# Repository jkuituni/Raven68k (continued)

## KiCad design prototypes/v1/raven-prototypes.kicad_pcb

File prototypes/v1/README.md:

# Raven68k Prototype Build

## Revision 0
This is the first publicly available release of the Raven68k project as generated and sent to [JLCPCB (Shenzhen JLC Electronics Co., Ltd.)](https://jlcpcb.com) for manufacture on November 5th, 2018.  As this is the very first prototype board, one should expect things that don't make sense or are outright wrong.  You have been warned. ;)

## Software 

The Rev0 software is available in this repository under the /rom/v1 directory.

## RAM and ROM locations

| Type 	| Start Address 	| Size   	|
|------	|---------------	|--------	|
| RAM  	| $000000       	| 1 MiB  	|
| ROM  	| $FFFF00       	| 64 KiB 	|

## Device Select Logic

Each peripheral has 64 bytes (32 words) of address space available to it.  As the 68681 has 16 registers, it is only using 1/2 of the available space.  This probably has the unintended effect of mirroring into the unused half of I/O space, making it unavailable for other use.

| Decimal | Hexadecimal | Device     |
|---------|-------------|------------|
| 1048576 |   $100000   | Dual UART  |
| 1048704 |   $100080   | Unassigned |
| 1048832 |   $100100   | Unassigned |
| 1048960 |   $100180   | Unassigned |
| 1049088 |   $100200   | Unassigned |
| 1049216 |   $100280   | Unassigned |
| 1049344 |   $100300   | Unassigned |
| 1049472 |   $100380   | Unassigned |

## Errata

### ROM Decoding logic
 ROM decoding is enabled when lines A17-A23 are high.  It should be active when lines **A16**-A23 are high. This can be solved by feeding A16 into pin 12 on U11 and cutting the +5V trace that leads to it.
 
 ### I/O Space Decoding Logic
 
 I/O space decoding is supposed to be immediately above the 1MiB RAM. This translates into 
 
     NOT(ROM_CS) AND A16=HIGH

The NAND gate (U11B) is not necessary and should be removed. All of this can be hooked directly to the 74HC138 (U13)

### Map ROM to RAM for boot

The system is missing a logic chip that maps the ROM into the bottom 64k of memory for the first 8 cycles so the boot sequence can happen.  This can be implemented by using an 8 bit shift register (74HC164) as in [Motorola Application Note AN897](http://retronik.fr/motorola/68K/68000/AN897_MC68008_minimum_configuration_system_%5BMotorola_1984_12p%5D.pdf) 

### Corrected Schematic
A corrected schematic will be made available once the errors have all been corrected and validated.

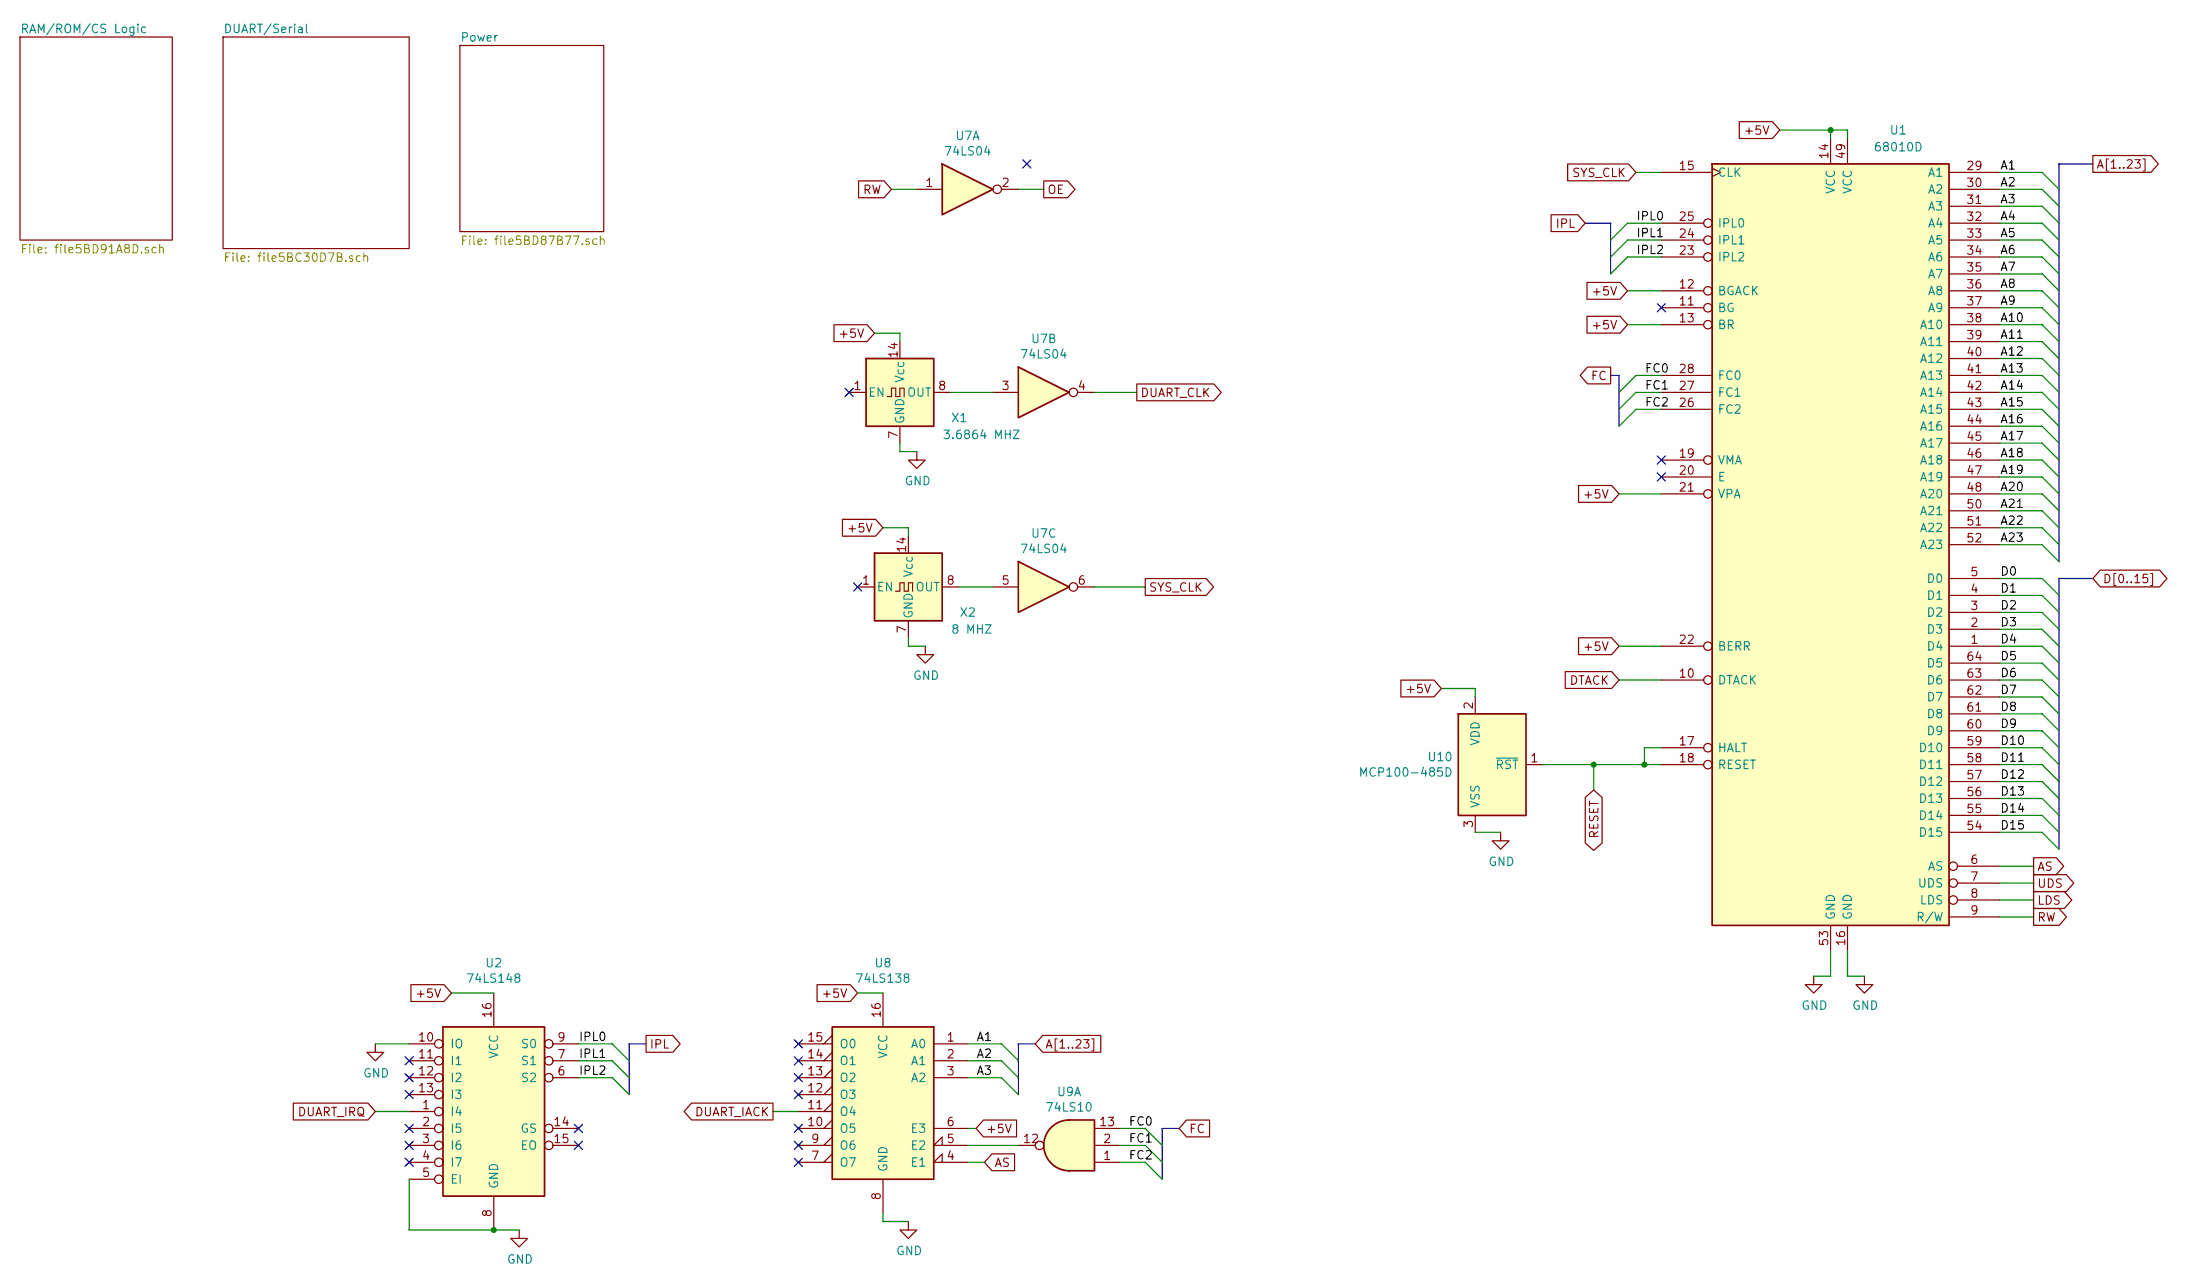
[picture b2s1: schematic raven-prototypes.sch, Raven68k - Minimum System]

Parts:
U1: 68010D; DIP-64_W22.86mm
U2: 74LS148
U7: 74LS04
U8: 74LS138
U9: 74LS10
U10: MCP100-485D
X1: 3.6864 MHZ
X2: 8 MHZ

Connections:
+5V: U1.12 (BGACK), U1.13 (BR), U1.14 (VCC), U1.21 (VPA), U1.22 (BERR), U1.49 (VCC), U2.16 (VCC), U8.6 (E3), U8.16 (VCC), U10.2 (VDD), X1.14 (Vcc), X2.14 (Vcc); also elsewhere on the board
/FC0: U1.28 (FC0), U9.13
/FC1: U1.27 (FC1), U9.2
/FC2: U1.26 (FC2), U9.1
/IPL0: U1.25 (IPL0), U2.9 (S0)
/IPL1: U1.24 (IPL1), U2.7 (S1)
/IPL2: U1.23 (IPL2), U2.6 (S2)
A1: U1.29 (A1), U8.1 (A0); also elsewhere on the board
A2: U1.30 (A2), U8.2 (A1); also elsewhere on the board
A3: U1.31 (A3), U8.3 (A2); also elsewhere on the board
A4: U1.32 (A4); also elsewhere on the board
A5: U1.33 (A5); also elsewhere on the board
A6: U1.34 (A6); also elsewhere on the board
A7: U1.35 (A7); also elsewhere on the board
A8: U1.36 (A8); also elsewhere on the board
A9: U1.37 (A9); also elsewhere on the board
A10: U1.38 (A10); also elsewhere on the board
A11: U1.39 (A11); also elsewhere on the board
A12: U1.40 (A12); also elsewhere on the board
A13: U1.41 (A13); also elsewhere on the board
A14: U1.42 (A14); also elsewhere on the board
A15: U1.43 (A15); also elsewhere on the board
A16: U1.44 (A16); also elsewhere on the board
A17: U1.45 (A17); also elsewhere on the board
A18: U1.46 (A18); also elsewhere on the board
A19: U1.47 (A19); also elsewhere on the board
A20: U1.48 (A20); also elsewhere on the board
A21: U1.50 (A21); also elsewhere on the board
A22: U1.51 (A22); also elsewhere on the board
A23: U1.52 (A23); also elsewhere on the board
AS: U1.6 (AS), U8.4 (E1)
D0: U1.5 (D0); also elsewhere on the board
D1: U1.4 (D1); also elsewhere on the board
D2: U1.3 (D2); also elsewhere on the board
D3: U1.2 (D3); also elsewhere on the board
D4: U1.1 (D4); also elsewhere on the board
D5: U1.64 (D5); also elsewhere on the board
D6: U1.63 (D6); also elsewhere on the board
D7: U1.62 (D7); also elsewhere on the board
D8: U1.61 (D8); also elsewhere on the board
D9: U1.60 (D9); also elsewhere on the board
D10: U1.59 (D10); also elsewhere on the board
D11: U1.58 (D11); also elsewhere on the board
D12: U1.57 (D12); also elsewhere on the board
D13: U1.56 (D13); also elsewhere on the board
D14: U1.55 (D14); also elsewhere on the board
D15: U1.54 (D15); also elsewhere on the board
DTACK: U1.10 (DTACK); also elsewhere on the board
DUART_CLK: U7.4; also elsewhere on the board
DUART_IACK: U8.11 (O4); also elsewhere on the board
DUART_IRQ: U2.1 (I4); also elsewhere on the board
GND: U1.16 (GND), U1.53 (GND), U2.5 (EI), U2.8 (GND), U2.10 (IO), U8.8 (GND), U10.3 (VSS), X1.7 (GND), X2.7 (GND); also elsewhere on the board
LDS: U1.8 (LDS); also elsewhere on the board
unnamed: U7.3, X1.8 (OUT)
unnamed: U7.5, X2.8 (OUT)
unnamed: U8.5 (E2), U9.12
OE: U7.2; also elsewhere on the board
RESET: U1.17 (HALT), U1.18 (RESET), U10.1 (~RST); also elsewhere on the board
RW: U1.9 (R/W), U7.1; also elsewhere on the board
SYS_CLK: U1.15 (CLK), U7.6
UDS: U1.7 (UDS); also elsewhere on the board

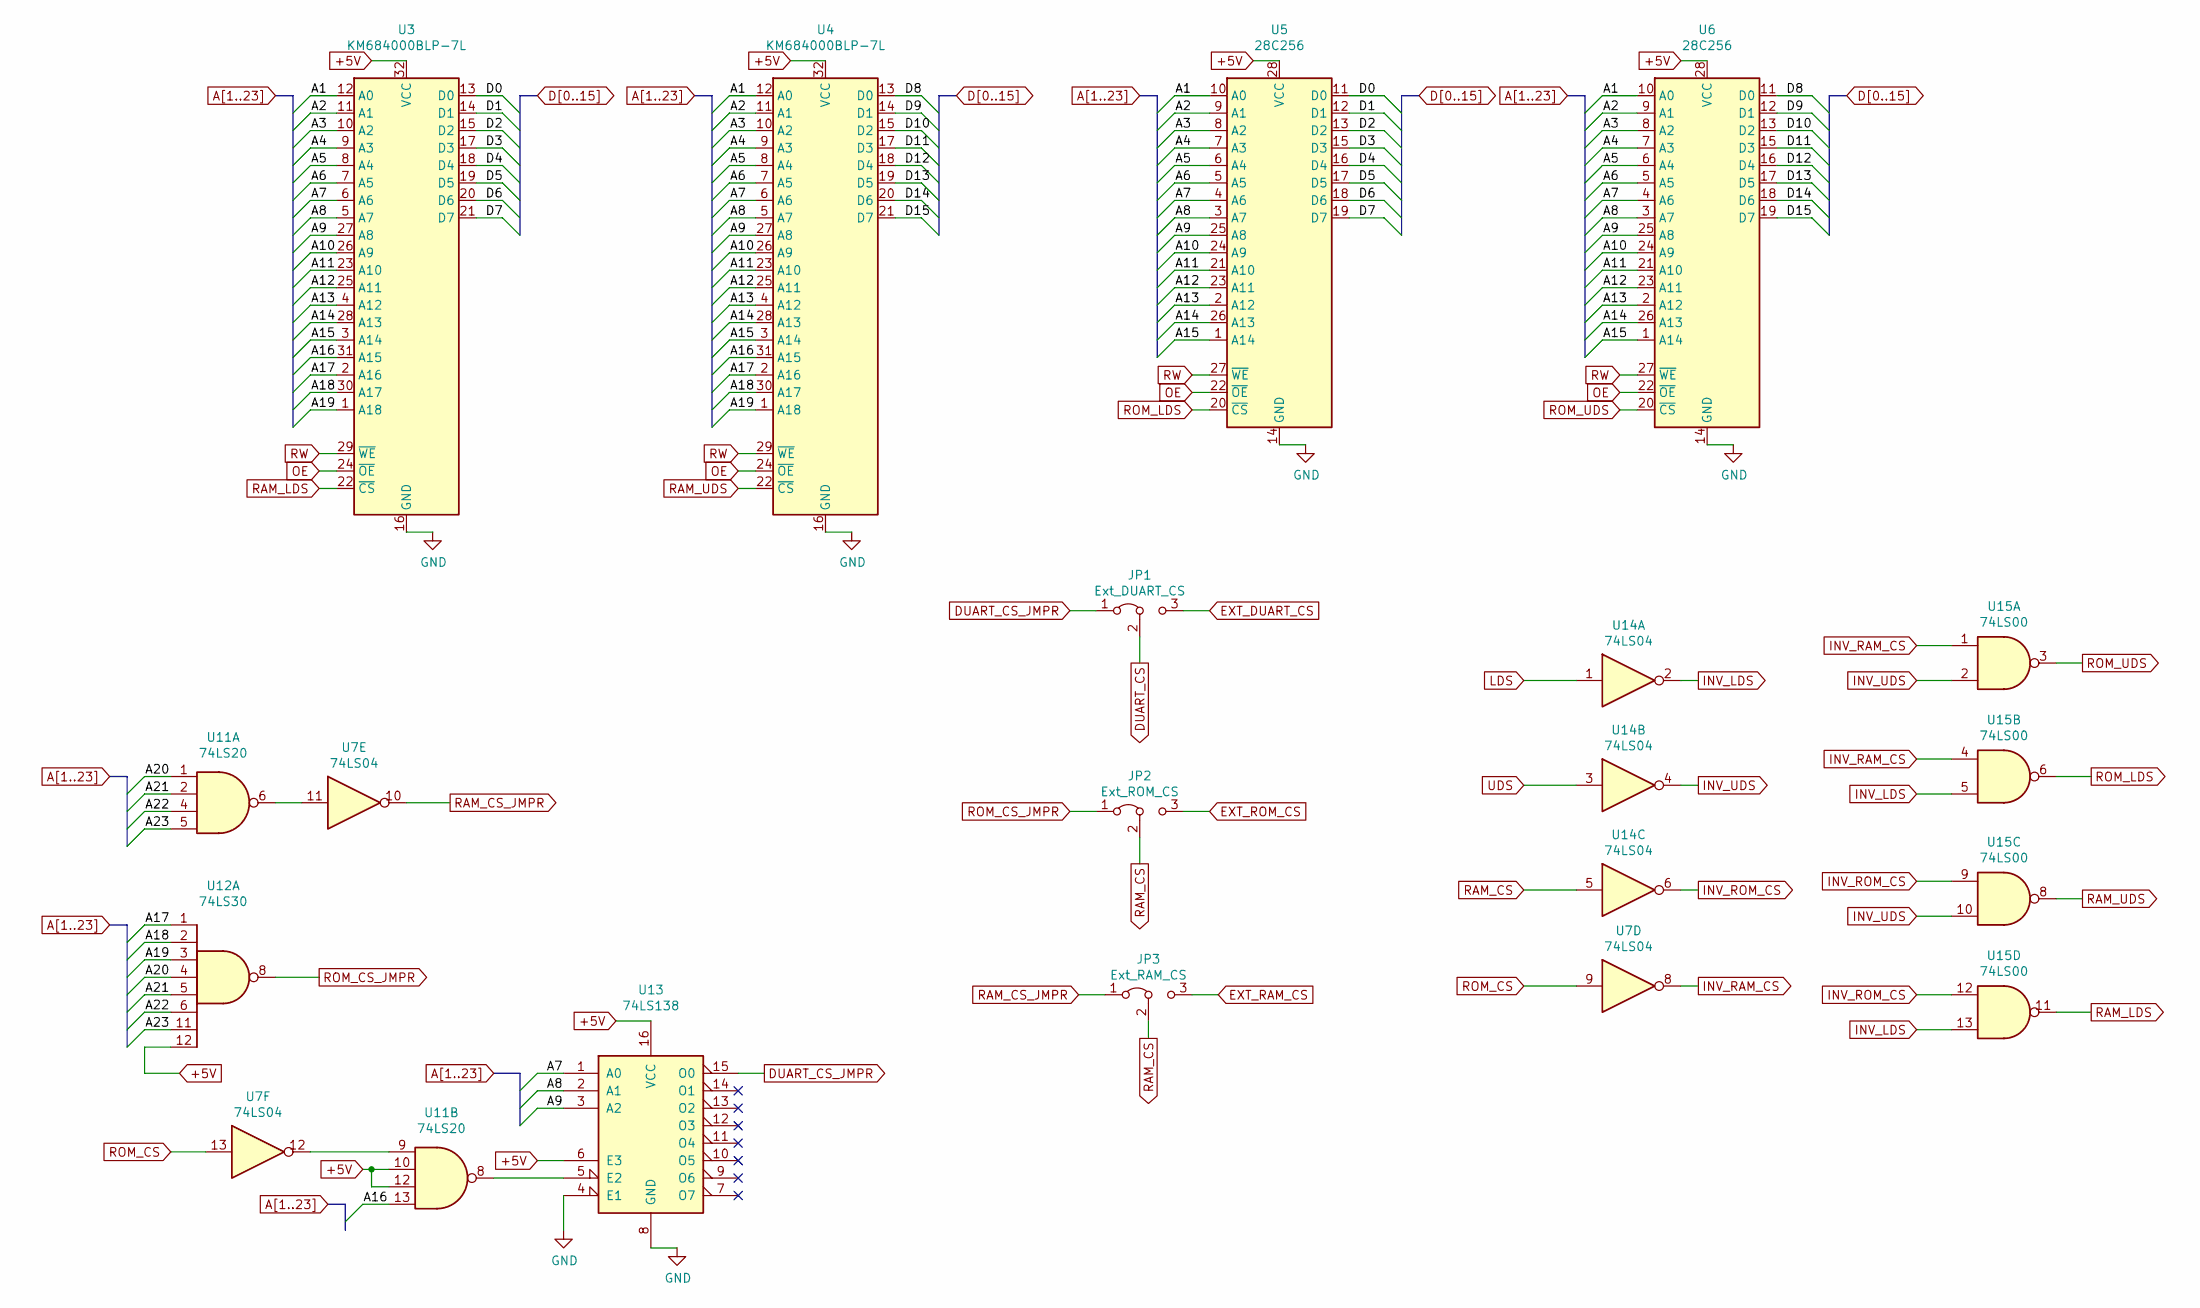
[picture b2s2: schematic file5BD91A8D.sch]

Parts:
JP1: Ext_DUART_CS
JP2: Ext_ROM_CS
JP3: Ext_RAM_CS
U3, U4: KM684000BLP-7L; DIP-32_W15.24mm
U5, U6: 28C256; DIP-28_W15.24mm
U7, U14: 74LS04
U11: 74LS20
U12: 74LS30
U13: 74LS138
U15: 74LS00

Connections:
+5V: U3.32 (VCC), U4.32 (VCC), U5.28 (VCC), U6.28 (VCC), U11.10, U11.12, U12.12, U13.6 (E3), U13.16 (VCC); also elsewhere on the board
A1: U3.12 (A0), U4.12 (A0), U5.10 (A0), U6.10 (A0); also elsewhere on the board
A2: U3.11 (A1), U4.11 (A1), U5.9 (A1), U6.9 (A1); also elsewhere on the board
A3: U3.10 (A2), U4.10 (A2), U5.8 (A2), U6.8 (A2); also elsewhere on the board
A4: U3.9 (A3), U4.9 (A3), U5.7 (A3), U6.7 (A3); also elsewhere on the board
A5: U3.8 (A4), U4.8 (A4), U5.6 (A4), U6.6 (A4); also elsewhere on the board
A6: U3.7 (A5), U4.7 (A5), U5.5 (A5), U6.5 (A5); also elsewhere on the board
A7: U3.6 (A6), U4.6 (A6), U5.4 (A6), U6.4 (A6), U13.1 (A0); also elsewhere on the board
A8: U3.5 (A7), U4.5 (A7), U5.3 (A7), U6.3 (A7), U13.2 (A1); also elsewhere on the board
A9: U3.27 (A8), U4.27 (A8), U5.25 (A8), U6.25 (A8), U13.3 (A2); also elsewhere on the board
A10: U3.26 (A9), U4.26 (A9), U5.24 (A9), U6.24 (A9); also elsewhere on the board
A11: U3.23 (A10), U4.23 (A10), U5.21 (A10), U6.21 (A10); also elsewhere on the board
A12: U3.25 (A11), U4.25 (A11), U5.23 (A11), U6.23 (A11); also elsewhere on the board
A13: U3.4 (A12), U4.4 (A12), U5.2 (A12), U6.2 (A12); also elsewhere on the board
A14: U3.28 (A13), U4.28 (A13), U5.26 (A13), U6.26 (A13); also elsewhere on the board
A15: U3.3 (A14), U4.3 (A14), U5.1 (A14), U6.1 (A14); also elsewhere on the board
A16: U3.31 (A15), U4.31 (A15), U11.13; also elsewhere on the board
A17: U3.2 (A16), U4.2 (A16), U12.1; also elsewhere on the board
A18: U3.30 (A17), U4.30 (A17), U12.2; also elsewhere on the board
A19: U3.1 (A18), U4.1 (A18), U12.3; also elsewhere on the board
A20: U11.1, U12.4; also elsewhere on the board
A21: U11.2, U12.5; also elsewhere on the board
A22: U11.4, U12.6; also elsewhere on the board
A23: U11.5, U12.11; also elsewhere on the board
D0: U3.13 (D0), U5.11 (D0); also elsewhere on the board
D1: U3.14 (D1), U5.12 (D1); also elsewhere on the board
D2: U3.15 (D2), U5.13 (D2); also elsewhere on the board
D3: U3.17 (D3), U5.15 (D3); also elsewhere on the board
D4: U3.18 (D4), U5.16 (D4); also elsewhere on the board
D5: U3.19 (D5), U5.17 (D5); also elsewhere on the board
D6: U3.20 (D6), U5.18 (D6); also elsewhere on the board
D7: U3.21 (D7), U5.19 (D7); also elsewhere on the board
D8: U4.13 (D0), U6.11 (D0); also elsewhere on the board
D9: U4.14 (D1), U6.12 (D1); also elsewhere on the board
D10: U4.15 (D2), U6.13 (D2); also elsewhere on the board
D11: U4.17 (D3), U6.15 (D3); also elsewhere on the board
D12: U4.18 (D4), U6.16 (D4); also elsewhere on the board
D13: U4.19 (D5), U6.17 (D5); also elsewhere on the board
D14: U4.20 (D6), U6.18 (D6); also elsewhere on the board
D15: U4.21 (D7), U6.19 (D7); also elsewhere on the board
DUART_CS: JP1.2 (C); also elsewhere on the board
DUART_CS_JMPR: JP1.1 (A), U13.15 (O0)
EXT_DUART_CS: JP1.3 (B); also elsewhere on the board
EXT_RAM_CS: JP3.3 (B); also elsewhere on the board
EXT_ROM_CS: JP2.3 (B); also elsewhere on the board
GND: U3.16 (GND), U4.16 (GND), U5.14 (GND), U6.14 (GND), U13.4 (E1), U13.8 (GND); also elsewhere on the board
INV_LDS: U14.2, U15.5, U15.13
INV_RAM_CS: U7.8, U15.1, U15.4
INV_ROM_CS: U14.6, U15.9, U15.12
INV_UDS: U14.4, U15.2, U15.10
LDS: U14.1; also elsewhere on the board
unnamed: U7.11, U11.6
unnamed: U11.8, U13.5 (E2)
unnamed: U7.12, U11.9
OE: U3.24 (~OE), U4.24 (~OE), U5.22 (~OE), U6.22 (~OE); also elsewhere on the board
RAM_CS: JP2.2 (C), JP3.2 (C), U14.5
RAM_CS_JMPR: JP3.1 (A), U7.10
RAM_LDS: U3.22 (~CS), U15.11
RAM_UDS: U4.22 (~CS), U15.8
ROM_CS: U7.9, U7.13
ROM_CS_JMPR: JP2.1 (A), U12.8
ROM_LDS: U5.20 (~CS), U15.6
ROM_UDS: U6.20 (~CS), U15.3
RW: U3.29 (~WE), U4.29 (~WE), U5.27 (~WE), U6.27 (~WE); also elsewhere on the board
UDS: U14.3; also elsewhere on the board

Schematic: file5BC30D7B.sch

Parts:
J1: Serial_Connections
J2: Ext_Signal
U16: 68681; DIP-40_W15.24mm
U17, U18: MAX233-DIP

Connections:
+5V: U16.40 (VCC), U17.7, U18.7; also elsewhere on the board
A1: U16.1 (RS1); also elsewhere on the board
A2: U16.3 (RS2); also elsewhere on the board
A3: U16.5 (RS3); also elsewhere on the board
A4: U16.6 (RS4); also elsewhere on the board
A16: J2.7; also elsewhere on the board
A17: J2.8; also elsewhere on the board
A18: J2.9; also elsewhere on the board
A19: J2.10; also elsewhere on the board
A20: J2.11; also elsewhere on the board
A21: J2.12; also elsewhere on the board
A22: J2.13; also elsewhere on the board
A23: J2.14; also elsewhere on the board
CTS-A: U16.7 (IP0), U17.20
CTS-A-SERIAL: J1.4, U17.19
CTS-B: U16.4 (IP1), U18.20
CTS-B-SERIAL: J1.8, U18.19
D0: U16.25 (D0); also elsewhere on the board
D1: U16.16 (D1); also elsewhere on the board
D2: U16.24 (D2); also elsewhere on the board
D3: U16.17 (D3); also elsewhere on the board
D4: U16.23 (D4); also elsewhere on the board
D5: U16.18 (D5); also elsewhere on the board
D6: U16.22 (D6); also elsewhere on the board
D7: U16.19 (D7); also elsewhere on the board
DTACK: U16.9 (DTACK); also elsewhere on the board
DUART_CLK: U16.32 (X1/CLK); also elsewhere on the board
DUART_CS: U16.35 (CS); also elsewhere on the board
DUART_IACK: U16.37 (IACK); also elsewhere on the board
DUART_IRQ: U16.21 (IRQ); also elsewhere on the board
EXT_DUART_CS: J2.3; also elsewhere on the board
EXT_RAM_CS: J2.2; also elsewhere on the board
EXT_ROM_CS: J2.1; also elsewhere on the board
GND: U16.20 (GND), U17.6, U17.9, U18.6, U18.9; also elsewhere on the board
LDS: J2.5; also elsewhere on the board
unnamed: U17.10, U17.16
unnamed: U17.11, U17.15
unnamed: U17.12, U17.17
unnamed: U18.10, U18.16
unnamed: U18.11, U18.15
unnamed: U18.12, U18.17
RESET: U16.34 (RESET); also elsewhere on the board
RTS-A: U16.29 (OP0), U17.1
RTS-A-SERIAL: J1.3, U17.18
RTS-B: U16.12 (OP1), U18.1
RTS-B-SERIAL: J1.7, U18.18
RW: U16.8 (R/W); also elsewhere on the board
RxD-A: U16.31 (RXDA), U17.3
RxD-A-SERIAL: J1.2, U17.4
RxD-B: U16.10 (RXDB), U18.3
RxD-B-SERIAL: J1.6, U18.4
TxD-A: U16.30 (TXDA), U17.2
TxD-A-SERIAL: J1.1, U17.5
TxD-B: U16.11 (TXDB), U18.2
TxD-B-SERIAL: J1.5, U18.5
UDS: J2.4; also elsewhere on the board

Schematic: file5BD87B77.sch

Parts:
C1: C; C_Disc_D6.0mm_W4.4mm_P5.00mm
C2, C3, C4, C5, C6, C7, C8, C9, C10, C11, C12, C13, C14, C15, C16: C
J3: 770997-1
U7, U14: 74LS04
U9: 74LS10
U11: 74LS20
U12: 74LS30
U15: 74LS00

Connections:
+5V: C1.1, C2.1, C3.1, C4.1, C5.1, C6.1, C7.1, C8.1, C9.1, C10.1, C11.1, C12.1, C13.1, C14.1, C15.1, C16.1, J3.4, U7.14 (VCC), U9.14 (VCC), U11.14 (VCC), U12.14 (VCC), U14.14 (VCC), U15.14 (VCC); also elsewhere on the board
GND: C1.2, C2.2, C3.2, C4.2, C5.2, C6.2, C7.2, C8.2, C9.2, C10.2, C11.2, C12.2, C13.2, C14.2, C15.2, C16.2, J3.2, J3.3, U7.7 (GND), U9.7 (GND), U11.7 (GND), U12.7 (GND), U14.7 (GND), U15.7 (GND); also elsewhere on the board

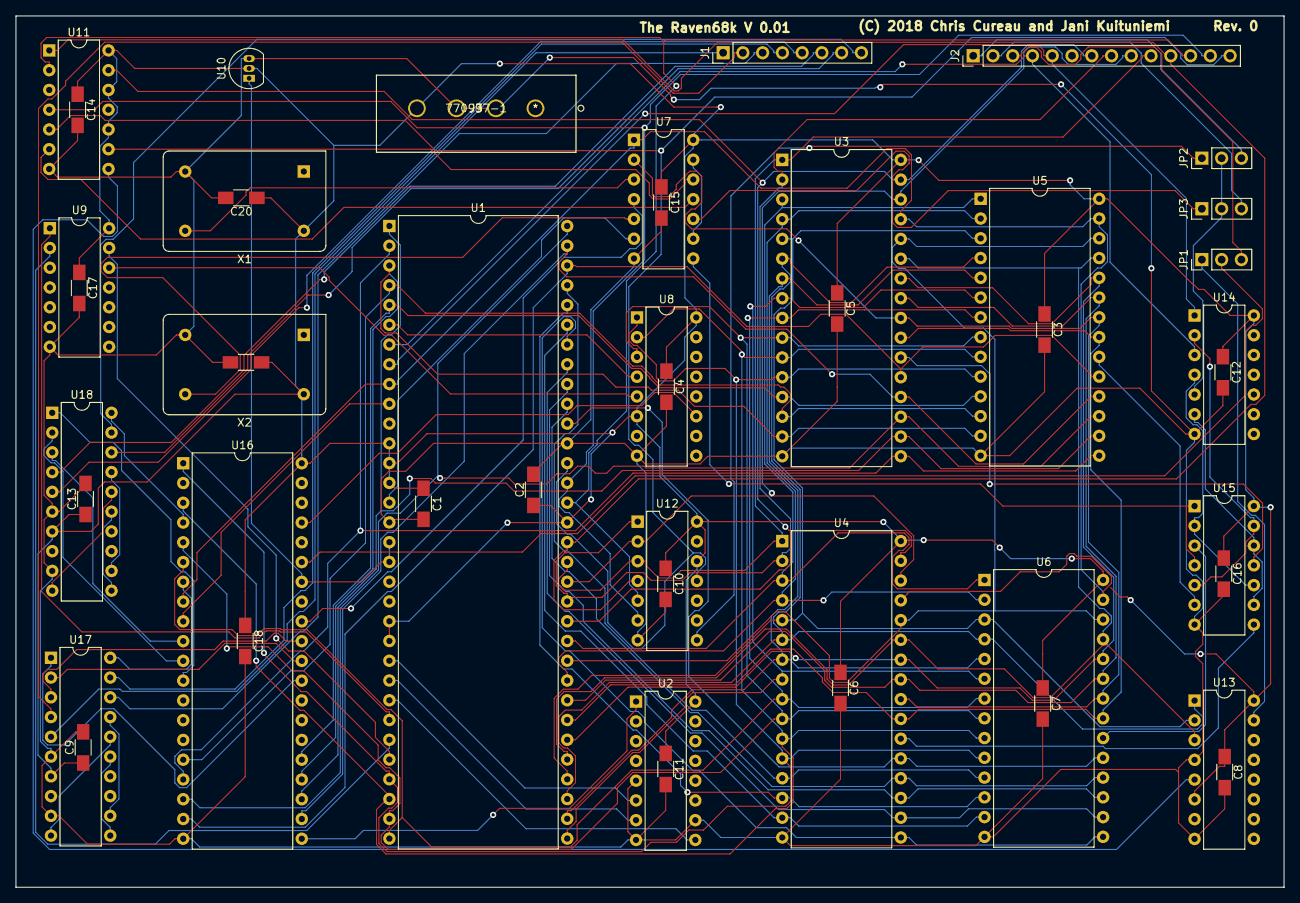
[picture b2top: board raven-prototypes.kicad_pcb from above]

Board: 2 copper layers, 163.0 x 112.0 mm, 46 parts (0 on the bottom side), 103 nets.

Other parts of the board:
C17, C18, C19, C20: C; C_1206_HandSoldering

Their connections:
+5V: C17.1, C18.1, C19.1, C20.1; also elsewhere on the board
GND: C17.2, C18.2, C19.2, C20.2; also elsewhere on the board

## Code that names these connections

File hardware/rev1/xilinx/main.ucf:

#PACE: Start of Constraints generated by PACE

#PACE: Start of PACE I/O Pin Assignments
NET "ah<20>"  LOC = "P13"  ;
NET "ah<21>"  LOC = "P12"  ;
NET "ah<22>"  LOC = "P8"  ;
NET "ah<23>"  LOC = "P7"  ;
NET "al<1>"  LOC = "P19"  ;
NET "al<2>"  LOC = "P18"  ;
NET "al<3>"  LOC = "P14"  ;
NET "as"  LOC = "P1"  ; 
NET "dtack"  LOC = "P27"  ;
NET "duart_ce"  LOC = "P40"  ;
NET "duart_dtack"  LOC = "P28"  ;
NET "duart_iack"  LOC = "P34"  ;
NET "fc<0>"  LOC = "P5"  ;
NET "fc<1>"  LOC = "P3"  ; 
NET "fc<2>"  LOC = "P2"  ; 
NET "lds"  LOC = "P20"  ;
NET "oe"  LOC = "P33"  ;
NET "ram_lce"  LOC = "P39"  ;
NET "ram_uce"  LOC = "P38"  ;
NET "rom_lce"  LOC = "P37"  ;
NET "rom_uce"  LOC = "P36"  ;
NET "rtc_ce"  LOC = "P42"  ;
NET "rw"  LOC = "P6"  ;
NET "uds"  LOC = "P22"  ;
NET "we"  LOC = "P29"  ;

#PACE: Start of PACE Area Constraints

#PACE: Start of PACE Prohibit Constraints

#PACE: End of Constraints generated by PACE

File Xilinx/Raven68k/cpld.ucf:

#PACE: Start of Constraints generated by PACE

#PACE: Start of PACE I/O Pin Assignments
NET "a17"  LOC = "P18"  ;
NET "a21"  LOC = "P19"  ;
NET "a7"  LOC = "P13"  ;
NET "a8"  LOC = "P14"  ;
NET "a9"  LOC = "P16"  ;
NET "as"  LOC = "P6"  ;
NET "berr"  LOC = "P31"  ;
NET "clk"  LOC = "P43"  ;
NET "clk_out"  LOC = "P44"  ;
NET "dtack_out"  LOC = "P37"  ;
NET "duart_cs"  LOC = "P32"  ;
NET "duart_dtack"  LOC = "P2"  ;
NET "duart_irq"  LOC = "P3"  ;
NET "e"  LOC = "P12"  ;
NET "ipl<0>"  LOC = "P22"  ;
NET "ipl<1>"  LOC = "P21"  ;
NET "ipl<2>"  LOC = "P20"  ;
NET "lds"  LOC = "P7"  ;
NET "oe"  LOC = "P23"  ;
NET "ram_evn_cs"  LOC = "P29"  ;
NET "ram_odd_cs"  LOC = "P30"  ;
NET "rom_evn_cs"  LOC = "P27"  ;
NET "rom_odd_cs"  LOC = "P28"  ;
NET "rw"  LOC = "P5"  ;
NET "uds"  LOC = "P8"  ;

#PACE: Start of PACE Area Constraints

#PACE: Start of PACE Prohibit Constraints

#PACE: End of Constraints generated by PACE

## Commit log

2018-01-08 Initial commit of Raven 68k schematics in KiCad format. Work-in-progressgit add .
2018-01-08 Expanded the readme.
2018-01-09 Added the Xilinx CPLD for managing the CPU signals and RAM/ROM control.
2018-01-09 Added 68681 DUART.
2018-01-09 Added a few pull-down resistors. Continued schematic re-work started in earlier commit.
2018-01-09 Fixed an issue with un-connected address pins a16..a19 and wrong address pin numbering on the RSx register select pins on the 68681.
2018-01-21 Initial implementation of system controller CPLD.
2018-01-21 Updated the Readme.
2018-01-21 Added missing RTC IRQ handling.
2018-01-21 Added LDS condition to RTC chip selection logic.
2018-01-21 Fixed memory decoding conditions so that whether or not IRQ is being served, it will still do the job.
2018-01-21 replace WE pin with OE = not R/W
2018-01-22 hierarchial sheets
2018-01-22 Update component library paths
2018-01-22 fix library paths
2018-05-30 misspell. =)
2018-06-25 sbc v1 verilog code
2018-06-25 memory mapping passes
2018-06-25 begin dtack
2018-06-25 first pass at dtack testbed
2018-06-26 all modules done
2018-06-26 start main
2018-06-26 move more into main
2018-06-27 main complete
2018-07-01 first pass at cpld logic. Pins not assigned yet
2018-07-01 couple of changes
2018-07-01 added pinouts for QF44
2018-07-02 release /CS when not needed
2018-07-02 mem_decoder watching wrong edge
2018-07-02 fix inout signals
2018-07-02 add component defs
2018-07-02 final test version
2018-07-03 ready to test v1
2018-07-03 clean up
2018-07-03 Xilinx cleanup
2018-07-03 don't include Xilinx data files
2018-07-05 memory mapping incorrect
2018-07-08 C:/Program Files (x86)/Git/AS not driving /CS or /DTACK correctly
2018-07-09 another test
2018-07-20 begin update for schematic
2018-09-07 oops...
2018-10-08 kprintf working, IDEATA interface started
2018-10-10 add prototype
2018-10-11 v1 schematic upates
2018-10-11 finish logic
2018-10-30 optimized logic
2018-11-05 gerbers created, Rev 0 sent to manufacturer
2018-11-08 added README
2021-03-09 out with the old, in with the new
2021-03-17 Initial draft of system control CPLD implementation in VHDL.
2021-03-25 organize files for revision 1
2021-03-25 prepare for schematics for rev1
2021-03-25 srec loading firmware
2021-03-25 Adding the Chartreuse monitor in polling mode
2021-03-26 Adjusted the I/O layout to avoid pins that are not available on the target CPLD dev board. Added handling of ROM overlay at low memory area during reset for 8 clocks and also adjusted memory decoding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
2021-03-28 Still need to work out pins on CPLD
2021-03-28 Initial Work-In-Progress draft version of the Firmware code for RAven68k. Contains functions to init the system, init the DUART, run RAM tests and Download & execute Motorola SRecord format binaries 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
2021-03-28 Formatting updates and bugfixes.
2021-03-28 Updated Readme.
2021-03-28 Updates to ReadMe.md files to divide and update the information per revision.
2021-03-28 Some more formatting and bug fixes.
2021-03-28 fixups for memory test in firmware, add toupper and tolower
2021-03-28 comments, formatting
2021-03-29 Couple of cleanups and altered ChkRam not to use stack at this point as we do not know whether or not RAM is good so safer not to use it. Instead, stashing the d1 value to d2 for the duration of the 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
2021-03-29 Fix to the ROM overlay at Reset condition logic.
2021-03-29 move from CLK to AS pulses for rom mapper
2021-03-30 Fix a bug in /AS counting. Should count to 4 rather than 8.
2021-03-30 breadboard prototype
2021-03-31 optimizations
2022-01-16 update vhdl
2022-01-17 Synthesis doesn't reflect real life
2022-01-23 working vhdl for my breadboard
2022-01-23 updated to new memory map
2022-01-25 Hopefully fixed the memory test issue and re-instated the check.
2022-01-25 fix memory test
2022-01-26 final fixup for ram test, fixup for srec loader
2022-01-31 update schematic for rev1
2022-01-31 working ehbasic
2022-02-01 use 38400,N81
2022-02-03 added buffers
2022-02-04 Adjust SRec upload routine.
2022-02-04 Removed unused toUpper/Lower() routines.
2022-02-06 upgrade to KiCad 6, first shot at layout
2022-02-06 Add datasheets for the ICs used in the design.
2022-02-06 Removed KiCAD backup files.
2022-02-06 Updated the README.md.
2022-02-06 Add forgotten register restoration and use of SRec loading address when executing the SRec.
2022-02-07 board layout complete, needs verification
2022-02-07 Initial integration of ROM monitor by Hayden Kroepfl into the Raven firmware ROM code. This is still work-in-progress and most likely further code adjustments are still needed.
2022-02-07 move components around
2022-02-08 first plot
2022-02-08 remove tiny leftover traces
2022-02-09 some helpful labels
2022-02-11 add board standoffs
2022-02-11 additional mounting standoff near pressure area
2022-02-13 still issues with monitor
2022-02-13 monitor working
2022-02-13 simple instructions
2022-02-13 comment easy68k testing stuff
2022-02-15 naming update for NOT_LDS
2022-02-16 first test with interrupts
2022-02-16 add vbr setting
2022-02-16 go full 68000 on this...
2022-02-16 stacks, stacks everywhere
2022-02-17 a5 gets overwritten!
2022-02-17 compile what should be a working interrupt monitor
2022-02-17 disable ram test
2022-02-17 replace RESET with STOP
2022-02-17 baud rate changes
2022-02-25 bad footprint on rev1
2022-02-25 don't add binaries
2022-02-27 add BOM
2023-10-31 Initial commit for Raven rev 2. Changes compared to the rev 1 are replacement of the SRAM memory with a single 72pin SIMM socket and to accommodate the requirement for writing a DRAM controller state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
2023-10-31 Added a README file.
2023-10-31 Minor correction to the README.
2023-10-31 Added a note on the README about what this revision is about.
2023-10-31 Added rev2 to the README.
2024-02-22 Fixed Bus connections. Added SIMM control connections to the CPLD. Added missing symbols from rev1 library. Cleaned up some SRAM related control signals that are no longer needed.
2024-02-22 Clean up of unneeded files.
2024-02-22 Added hierarchical labels from main sheet to RAM and ROM sheet.
2024-02-22 Added upper two bytes to SIMM connection. Updated the PCB at the same time.
2024-02-23 Added SIMM footprint and Raven logo. Did initial PCB component placement and routing using autorouter. Still needs to be checked before ordering PCBs to verify on an actual hardware.
2024-02-24 Minor tweaks to rev 1 files.
2024-02-24 Remove accidentally committed backup files.
2024-02-26 Re-structure of the repository to better reflect what is common across the revisions and what is not as well as to be perhaps a bit easier to follow what is where.
2024-02-26 Updated the README to reflect the new structure.
2024-02-26 Datasheet for the SIMM module by Micron.
2024-02-26 Fix linefeeds on README.
2024-02-26 Update README.md again to fix linefeeds.
2024-02-26 Update README.md for rev1
2024-02-26 README file for hardware/ directory.
2024-02-26 README for software/ directory.
2024-02-28 Minor adjustment to add the CLK signal to the CPLD that was forgotten. Re-did the PCB to reflect this change and also edited the component placement a bit.
2024-09-02 DRC fixes.
2024-09-02 ERC fixes, part 1
2024-11-08 ERC fixes part 2. No more errors reported. Re-routed the PCB.
2026-01-28 First version of main CPLD logic with DRAM controller integrated.
